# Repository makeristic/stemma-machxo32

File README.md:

# STEMMA QT MachXO2 breakout

A KiCad design for a Lattice MachXO2 FPGA breakout in a 32-pin QFN package, with two STEMMA QT I²C connectors, 3.3 V regulation, I²C level shifting, GPIO headers, and a DebugEdge programming connector.

This repository is a fork of [chickadee-tech/stemma-machxo32](https://github.com/chickadee-tech/stemma-machxo32). The original design is by Scott Shawcroft, with DebugEdge changes by Mark Olsson. Michael Cutler's fork adds suggested component part numbers to the schematic.

## Status

This is a historical hardware design from September–October 2020. The repository includes a schematic and routed two-layer PCB, but no assembled-board photos, test reports, fabrication exports, FPGA bitstream, or programming instructions. These files do not establish that the design has been built or electrically validated.

The [source audit](docs/code-audit-report.md) corrected the suggested FPGA part to **`LCMXO2-1200HC-4SG32I`**, matching the 32-pin QFN package, pin functions, and 3.3 V supply intent documented by [Lattice](https://www.latticesemi.com/view_document?document_id=38834). It also repaired DebugEdge schematic connections to agree with the existing PCB. Remaining footprint, clearance, thermal-pad, and licence questions still require review before manufacture or reuse.

## Files

* [KiCad project](stemma-mach32.pro), [legacy schematic](stemma-mach32.sch), [PCB layout](stemma-mach32.kicad_pcb), and [netlist](stemma-mach32.net). The filenames use `mach32`, while the repository name uses `machxo32`.
* [Symbol library table](sym-lib-table) and [footprint library table](fp-lib-table).
* [.gitmodules](.gitmodules), which describes the external `kicad-libs` and `debug-edge` libraries pinned as Git submodules.
* [Versioned historical symbol cache](stemma-mach32-cache.lib), preserving the symbols used for source checks.

Suggested component part numbers are embedded in the schematic fields; there is no standalone BOM CSV.

## Open or modify the design

Clone the fork with its pinned libraries. Public HTTPS submodule URLs avoid requiring SSH setup:

```sh
git clone --recurse-submodules https://github.com/makeristic/stemma-machxo32.git
cd stemma-machxo32
```

For an existing checkout, run `git submodule sync` followed by `git submodule update --init --recursive`.

Open `stemma-mach32.pro` in KiCad. The PCB records **KiCad 5.1.6**, with legacy `.pro` and `.sch` formats; import into a copy when using a newer version. The project tables use `${KIPRJMOD}` for the submodules and `${KISYSMOD}` for the standard KiCad footprint library, so install the corresponding KiCad libraries and check library paths before editing.

The submodules supply:

* [Chickadee Tech KiCad libraries](https://github.com/chickadee-tech/kicad-libs): the `lattice` symbols and `chickadee` footprints.
* [DebugEdge](https://github.com/debug-edge/DebugEdge): the `Connector_DebugEdge` symbols and footprints.

Review the schematic, FPGA part selection, power supplies, programming interface, and design rules before generating fabrication files. No HDL project or host I²C software is included.

## Feedback and related projects

This fork does not have Issues enabled. Submit [pull requests to this fork](https://github.com/makeristic/stemma-machxo32/pulls) for documentation or suggested-part corrections, including the commit, KiCad version, and component references. Changes intended for the original design should identify the upstream project and its authors.

Related Makeristic projects: [STM32WB55 Feather](https://github.com/makeristic/Feather_STM32WB55), [STUSB4500 USB-PD breakout](https://github.com/makeristic/STUSB4500_Breakout), and [KiCad library](https://github.com/makeristic/Makeristic-KiCad-Library).

## Licence and attribution

No licence for the top-level hardware design was found in this fork or in the upstream repository metadata during this review. It has therefore not been relicensed as MIT. Obtain the upstream authors' permission or a clear licence grant before relying on redistribution or reuse rights.

The pinned submodules carry their own terms: [Chickadee Tech's library is CC BY 4.0](https://github.com/chickadee-tech/kicad-libs/blob/114e708df9f8237ff84cfc5284e7f81555c1f4d6/LICENSE), and [DebugEdge uses Solderpad Hardware License 2.1](https://github.com/debug-edge/DebugEdge/blob/3c2c808082ba6d3af2069bf030e18878714d6500/LICENSE). The Chickadee library also excludes use of Chickadee Tech trademarks in its README. These terms are separate from this fork's design; third-party symbols, footprints, and marks are not granted new permissions by this README.

Standard cached symbols retain [KiCad's CC BY-SA 4.0 licence and exception](LICENSES/KiCad-Libraries.md); custom cached symbols retain the pinned submodules' terms. See the [audit](docs/code-audit-report.md) for exact source versions.

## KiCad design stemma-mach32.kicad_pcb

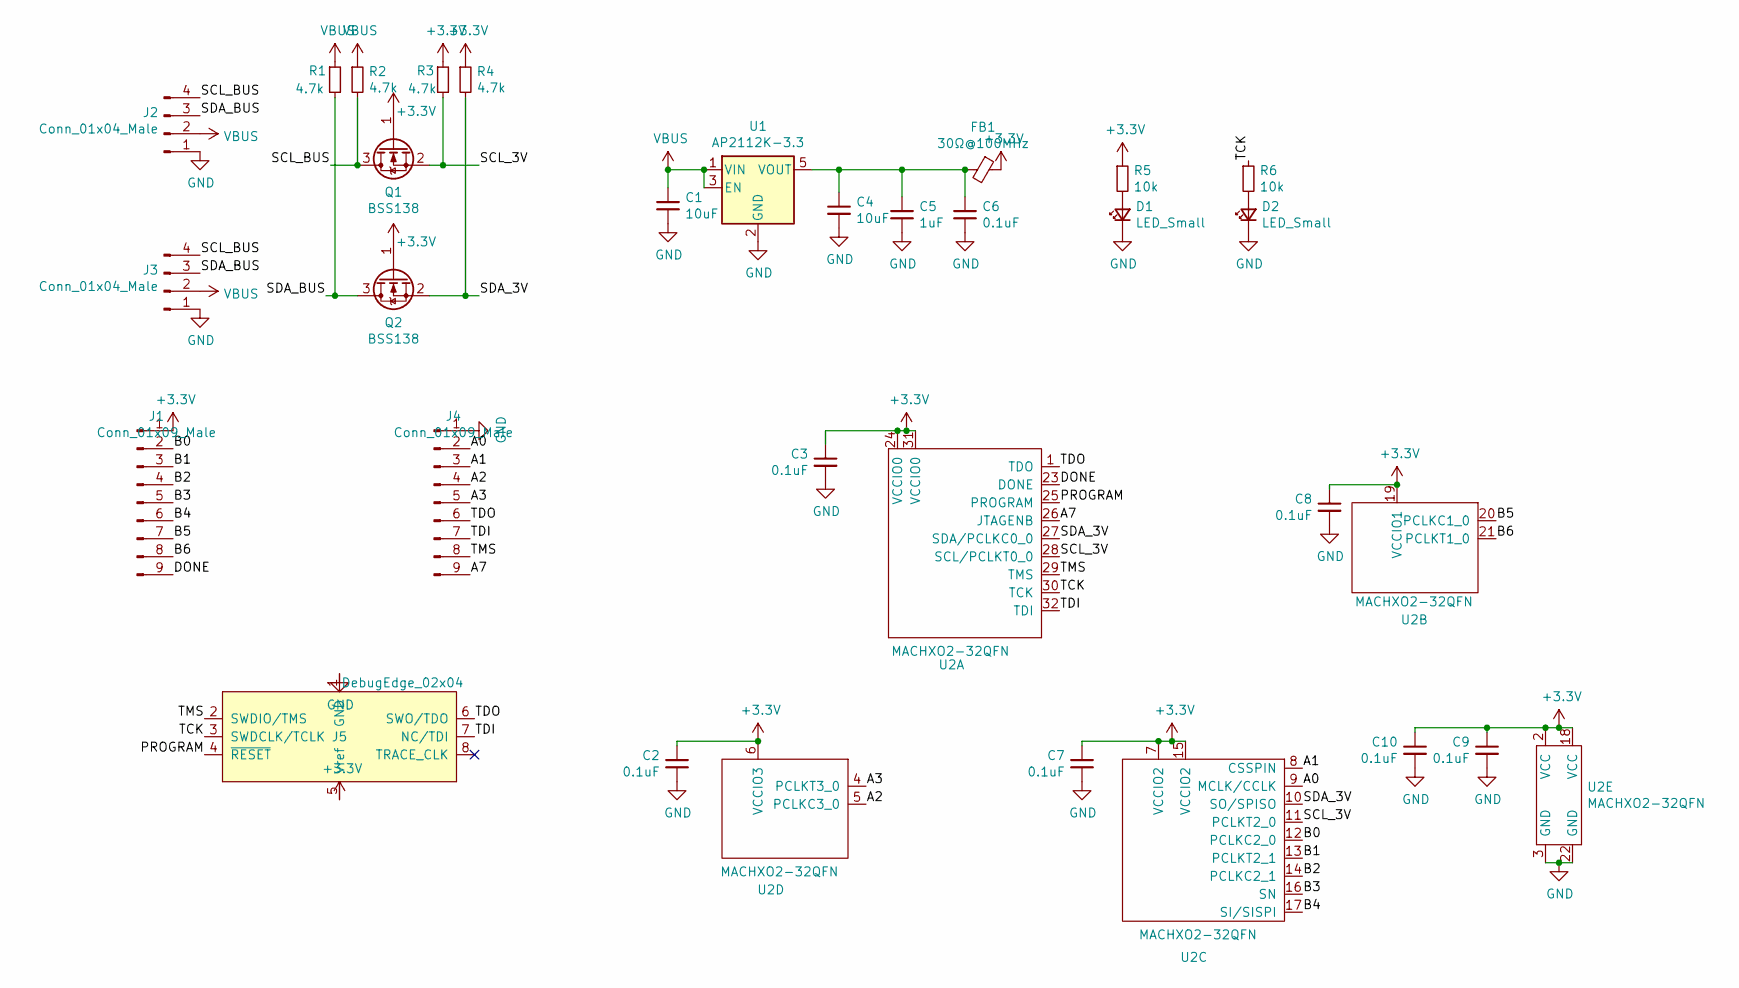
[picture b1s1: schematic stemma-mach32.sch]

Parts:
C1, C4: 10uF; C_0603_1608Metric_Pad1.05x0.95mm_HandSolder; Part # CL10A106KP8NNNC; LCSC Part # C19702
C2, C3, C6, C7, C8, C9, C10: 0.1uF; C_0603_1608Metric_Pad1.05x0.95mm_HandSolder; Part # CL10B104KC8NNNC; LCSC Part # C15725
C5: 1uF; C_0603_1608Metric_Pad1.05x0.95mm_HandSolder; Part # CL10A105KB8NNNC; LCSC Part # C15849
D1, D2: LED_Small; LED_0603_1608Metric_Pad1.05x0.95mm_HandSolder; Part # NCD0603A1; LCSC Part # C85323
FB1: 30Ω@100MHz; L_0603_1608Metric_Pad1.05x0.95mm_HandSolder; Part # BLM18PG300SN1D; LCSC Part # C17305
J1, J4: Conn_01x09_Male; PinHeader_1x09_P2.54mm_Vertical
J2, J3: Conn_01x04_Male; JST_SH_SM04B-SRSS-TB_1x04-1MP_P1.00mm_Horizontal
J5: DebugEdge_02x04; DebugEdge_2x04_Target
Q1, Q2: BSS138; SOT-23; Part # C426569; LCSC Part # C426569
R1, R2, R3, R4: 4.7k; R_0603_1608Metric_Pad1.05x0.95mm_HandSolder; Part # 0603WAF4701T5E; LCSC Part # C23162
R5, R6: 10k; R_0603_1608Metric_Pad1.05x0.95mm_HandSolder; Part # 0603WAF1002T5E; LCSC Part # C25804
U1: AP2112K-3.3; SOT-23-5; Part # AP2112K-3.3TRG1; LCSC Part # C51118
U2: MACHXO2-32QFN; QFN-32-1EP_5x5mm_P0.5mm_EP3.1x3.1mm; Part # LCMXO2-1200HC-4SG32I

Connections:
+3V3: C2.1, C3.1, C7.1, C8.1, C9.1, C10.1, FB1.1, J1.1, J5.5 (Vref), Q1.1 (G), Q2.1 (G), R3.1, R4.1, R5.1, U2.2 (VCC), U2.6 (VCCIO3), U2.7 (VCCIO2), U2.15 (VCCIO2), U2.18 (VCC), U2.19 (VCCIO1), U2.24 (VCCIO0), U2.31 (VCCIO0)
/A0: J4.2, U2.9 (MCLK/CCLK)
/A1: J4.3, U2.8 (CSSPIN)
/A2: J4.4, U2.5 (PCLKC3_0)
/A3: J4.5, U2.4 (PCLKT3_0)
/A7: J4.9, U2.26 (JTAGENB)
/B0: J1.2, U2.12 (PCLKC2_0)
/B1: J1.3, U2.13 (PCLKT2_1)
/B2: J1.4, U2.14 (PCLKC2_1)
/B3: J1.5, U2.16 (SN)
/B4: J1.6, U2.17 (SI/SISPI)
/B5: J1.7, U2.20 (PCLKC1_0)
/B6: J1.8, U2.21 (PCLKT1_0)
/DONE: J1.9, U2.23 (DONE)
/PROGRAM: J5.4 (~RESET~), U2.25 (PROGRAM)
/SCL_3V: Q1.2 (S), R3.2, U2.11 (PCLKT2_0), U2.28 (SCL/PCLKT0_0)
/SCL_BUS: J2.4, J3.4, Q1.3 (D), R2.2
/SDA_3V: Q2.2 (S), R4.2, U2.10 (SO/SPISO), U2.27 (SDA/PCLKC0_0)
/SDA_BUS: J2.3, J3.3, Q2.3 (D), R1.2
/TCK: J5.3 (SWDCLK/TCLK), R6.1, U2.30 (TCK)
/TDI: J4.7, J5.7 (NC/TDI), U2.32 (TDI)
/TDO: J4.6, J5.6 (SWO/TDO), U2.1 (TDO)
/TMS: J4.8, J5.2 (SWDIO/TMS), U2.29 (TMS)
GND: C1.2, C2.2, C3.2, C4.2, C5.2, C6.2, C7.2, C8.2, C9.2, C10.2, D1.1 (K), D2.1 (K), J2.1, J3.1, J4.1, J5.1 (GND), U1.2 (GND), U2.3 (GND), U2.22 (GND)
unnamed: C4.1, C5.1, C6.1, FB1.2, U1.5 (VOUT)
unnamed: D1.2 (A), R5.2
unnamed: D2.2 (A), R6.2
VBUS: C1.1, J2.2, J3.2, R1.1, R2.1, U1.1 (VIN), U1.3 (EN)

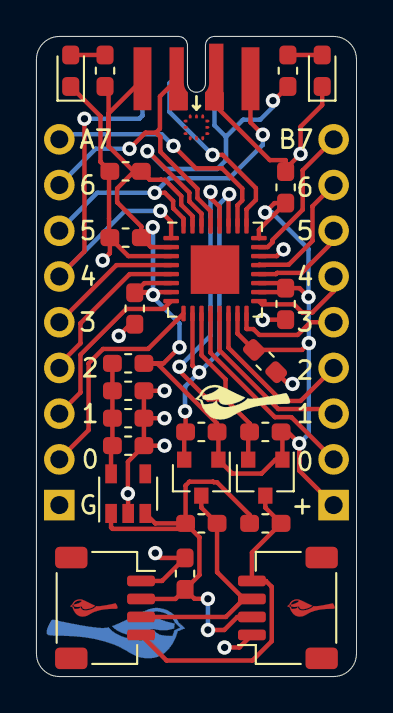
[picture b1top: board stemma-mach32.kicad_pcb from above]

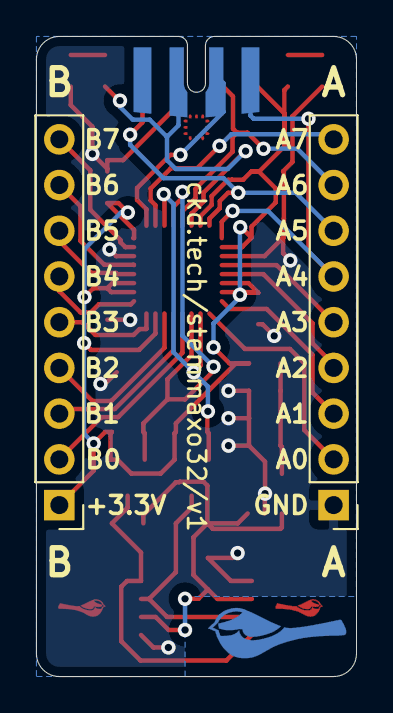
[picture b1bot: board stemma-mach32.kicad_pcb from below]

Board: 2 copper layers, 17.8 x 35.6 mm, 28 parts (2 on the bottom side), 28 nets.

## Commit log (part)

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2020-10-15 Added suggested part numbers to the BOM
